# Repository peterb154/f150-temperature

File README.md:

# Ford F150 Temperature Display System

A production-ready Ford F150 temperature display system using ESP32-S3 with CAN bus integration and TFT display. This project provides a clean, automotive-grade interface showing outside air temperature, HVAC driver/passenger temperature settings, and fan speed with pixel-perfect text centering and professional styling.

## 🚗 Project Overview

This system captures and displays real-time Ford F150 climate control data via CAN bus at 125 kbps. It features a modern 4-card layout optimized for readability and includes special handling for HVAC off states, simulation mode for testing, and optional CSV logging for data analysis.

### Key Features

- **Real-time Temperature Display** - OAT, driver/passenger HVAC temps, and fan speed
- **Professional UI** - 4-card layout with pixel-perfect text centering and TrueType fonts
- **HVAC State Handling** - Blank display for disabled/off climate controls
- **Simulation Mode** - Built-in test mode cycling through various temperature scenarios
- **Adaptive Backlight** - PWM brightness control based on console dimming level
- **Optional CSV Logging** - Data capture for serial visualization tools (toggleable)
- **Parameterized Design** - Easy customization of fonts, colors, and layout

## 📁 Project Structure

```text
.
├── src/
│   ├── main.cpp                  # Production temperature display system
│   └── main.cpp.save.logger      # Original CAN logger (backup)
├── include/
│   ├── pins.h                    # Hardware pin assignments
│   └── colors.h                  # TFT display color definitions
├── can_visual_grid.py            # Python visualization tool (legacy)
├── F150_*.md                     # Decoded system documentation
│   ├── F150_CONSOLE_LIGHTS.md
│   ├── F150_HVAC_FAN.md
│   ├── F150_HVAC_TEMP.md
│   └── F150_OAT.md
├── platformio.ini                # ESP32 build configuration
├── pyproject.toml               # Python dependencies (for analysis tools)
└── README.md                    # This documentation
```

## 🔧 Hardware Requirements

### ESP32 Temperature Display Setup

- **ESP32-S3 Development Board** (320KB RAM, 8MB Flash recommended)
- **CAN Transceiver Module** (WCMCU-230 or MCP2551)
- **ILI9341 TFT Display** (320x240, SPI interface)
- **XPT2046 Touch Controller** (optional, for future expansion)

### Pin Configuration

Pin assignments are defined in `include/pins.h`:

```cpp
// CAN Bus pins
#define CAN_TX_PIN 47
#define CAN_RX_PIN 48

// ILI9341 Display pins
#define TFT_CS   45
#define TFT_RST  0
#define TFT_DC   35
#define TFT_MOSI 36
#define TFT_CLK  37
#define TFT_LED  38  // Backlight control
#define TFT_MISO 39

// Touch Controller pins (XPT2046)
#define TOUCH_CLK  40
#define TOUCH_CS   41
#define TOUCH_DIN  42
#define TOUCH_DO   2
#define TOUCH_IRQ  1

// Status LED
#define STATUS_LED_PIN 15
```

### Vehicle Connection

- **CAN High**: Connect to vehicle's CAN H line (used connection to car stereo)
- **CAN Low**: Connect to vehicle's CAN L line (used connection to car stereo)
- **Ground**: Connect to vehicle chassis ground
- **Power**: 12V from vehicle (with appropriate regulation to 3.3V/5V)

⚠️ **Important**: Use proper CAN bus termination and isolation, the MCU-230 has a built-in termination resistor. Always test on a non-critical vehicle first.

## 💻 Software Setup

### ESP32 Temperature Display Firmware

1. **Clone the repository** and navigate to the project directory
2. **Install PlatformIO** (if not already installed)
3. **Build and upload** the temperature display firmware:

    ```bash
    # Upload to ESP32-S3
    pio run --target upload

    # Monitor serial output (optional)
    pio device monitor
    ```

4. **Connect hardware** according to pin configuration above
5. **Power on** - the system will auto-start in simulation mode for testing
6. **Connect to vehicle CAN bus** to see live temperature data

### Main System Components

#### `src/main.cpp` - Temperature Display System

The main firmware provides a production-ready Ford F150 temperature display with:

- **4-Card Layout**: OAT (top-left), Driver Temp, Fan Speed, Passenger Temp (bottom row)
- **CAN Bus Integration**: Decodes Ford F150 PIDs at 125 kbps
  - `0x3C4` - Outside Air Temperature (bytes 6-7)
  - `0x3C8` - HVAC Driver/Passenger Temps (ASCII encoded, bytes 0-3)
  - `0x357` - Fan Speed (7 levels, byte 1)
  - `0x3B3` - Console Dim Level (PWM backlight control, byte 3)
- **Smart Display Logic**: Blank temperatures when HVAC is off/disabled
- **Adaptive Backlight**: PWM brightness based on console dimming
- **Simulation Mode**: Built-in test scenarios for development/demo

#### `include/pins.h` - Hardware Configuration

Centralized pin assignments for ESP32-S3 connections.

#### `include/colors.h` - Display Theme

Defines the professional color scheme using 16-bit RGB565 format:

- **COLOR_BACKGROUND** (`0x0841`) - Dark blue-grey background
- **COLOR_CARD_BG** (`0x2124`) - Lighter grey for temperature cards
- **COLOR_PRIMARY** (`0x07FF`) - Cyan accent color
- **COLOR_TEXT** (`0xFFFF`) - White text
- **COLOR_SUCCESS/WARNING/HOT** - Status and temperature-based colors

Colors can be easily customized by modifying the hex values in this file.

## 📊 System Features

### Temperature Display Layout

**4-Card Professional Interface:**
- **OAT Card** (top-left): Outside Air Temperature with "OAT" label
- **DRIVER Card** (bottom-left): Driver HVAC temperature setting
- **FAN Card** (bottom-center): Visual fan speed bars (7 levels)
- **PASS Card** (bottom-right): Passenger HVAC temperature setting

### Smart Display Features

- **Pixel-Perfect Centering**: All temperature values are precisely centered using TrueType fonts
- **Blank State Handling**: Cards show blank when HVAC is off or controls are disabled
- **Adaptive Backlight**: Display brightness automatically adjusts based on console dimming
- **Professional Styling**: Rounded cards, consistent spacing, automotive-grade appearance

### HVAC State Detection

- **HVAC Off**: When driver temp is 0x00,0x00, display shows blank and fan speed goes to 0
- **Passenger Disabled**: Passenger temp shows blank when controls are disabled
- **Normal Operation**: All temperatures display with clean numeric values (no "F" suffix)
- **Fan Visualization**: Horizontal bars indicate fan speed levels 0-7

### Simulation Mode

**Built-in Test Scenarios** (6-second cycles):
1. **Normal Operation** - All temps active, fan running
2. **HVAC System Off** - Driver blank, fan 0, passenger may be active
3. **Passenger Disabled** - Passenger blank, driver/fan normal
4. **All HVAC Off** - Both temps blank, fan 0
5. **Mixed States** - Various combinations for testing

### Optional CSV Logging

**Data Capture for Analysis:**
- **Toggle Control**: Set `enableCSVLogging = true` in code
- **CSV Format**: Timestamp, CAN ID, raw bytes, decoded temperatures
- **Serial Output**: Compatible with visualization tools
- **Performance**: Minimal overhead when enabled, zero when disabled

## 🔍 CAN Bus Analysis Tools

For reverse-engineering additional Ford F150 systems and analyzing CAN bus data, see the comprehensive analysis tools documentation:

**[CAN_ANALYSIS_README.md](CAN_ANALYSIS_README.md)**

Includes:
- Interactive CAN message visualization (`can_visual_grid.py`)
- Raw CAN logger firmware
- Complete reverse-engineering workflow
- Decoded system documentation
- Temperature calibration tools

## 🛠️ Usage

### Normal Operation

1. **Power On**: System starts automatically and shows simulation data
2. **Connect to Vehicle**: CAN bus connection switches to live data
3. **Display Updates**: Temperature cards update in real-time (10Hz refresh)
4. **Backlight Control**: Display brightness adapts to console dimming

### Configuration Options

**CSV Logging** (in `main.cpp`):

```cpp
bool enableCSVLogging = false;  // Set to true for data capture
```

**Simulation Mode** (forced during development):

```cpp
bool forceSimulation = true;   // Set to false for vehicle connection
```

### Hardware Customization

- **Pin Assignments**: Modify `include/pins.h` for different ESP32 boards
- **Display Colors**: Customize `include/colors.h` for different themes
- **Card Layout**: Adjust constants at top of `main.cpp` for sizing/positioning

## 🛠️ Troubleshooting

### Display Issues

**Blank or corrupted display:**

- Check SPI connections to ILI9341 (see `pins.h`)
- Verify power supply stability (3.3V/5V)
- Ensure correct pin definitions match your hardware

**No temperature updates:**

- Verify vehicle is running (systems sleep when off)
- Check CAN H/L connections and polarity
- Monitor serial output for CAN message reception
- Try simulation mode first (`forceSimulation = true`)

**Backlight not working:**

- Check TFT_LED pin connection (see `pins.h`)
- Verify PWM output is functioning
- Test with manual brightness setting

### Performance Issues

**Slow or flickering display:**

- Check power supply current capacity
- Verify SPI clock speed settings
- Monitor for memory issues in serial output

**CAN bus connection problems:**

- Ensure 125 kbps baud rate
- Verify CAN transceiver (MCU-230 recommended)
- Check termination resistance (120Ω)

### Development Tips

1. **Start with simulation mode** - validates display without vehicle
2. **Monitor serial output** - shows CAN status and decoded values
3. **Use CSV logging** - captures data for offline analysis
4. **Test incrementally** - verify each system (display, CAN, decoding) separately

## 🤝 License

MIT License

---

## Ready for your F150 dashboard! 🚗📊

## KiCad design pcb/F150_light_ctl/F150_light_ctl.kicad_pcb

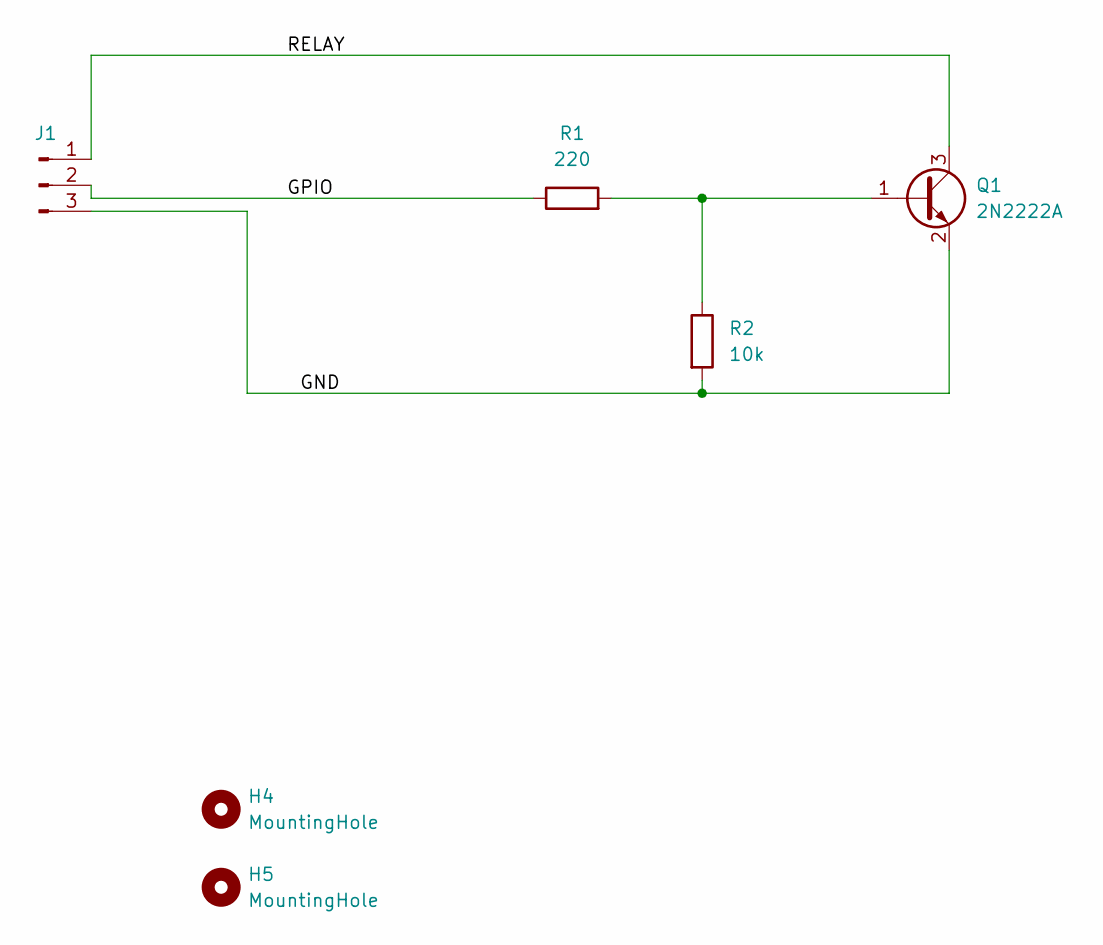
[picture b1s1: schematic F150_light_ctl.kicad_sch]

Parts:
H4, H5: MountingHole; MountingHole_3.5mm
J1: PinHeader_1x03_P2.54mm_Vertical
Q1: 2N2222A; SOT-23
R1: 220; R_0805_2012Metric
R2: 10k; R_0805_2012Metric

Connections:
/GND: J1.3, Q1.2 (E), R2.2
/GPIO: J1.2, R1.1
/RELAY: J1.1, Q1.3 (C)
unnamed: Q1.1 (B), R1.2, R2.1

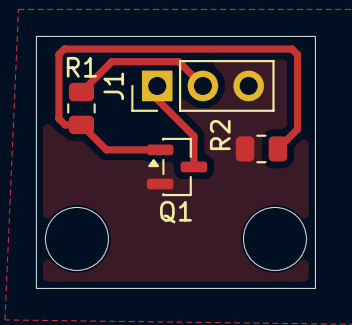
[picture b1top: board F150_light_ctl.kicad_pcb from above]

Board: 2 copper layers, 15.5 x 14.0 mm, 6 parts (0 on the bottom side), 4 nets.

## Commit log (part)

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2025-07-02 full logging
2025-07-03 working debugger
2025-07-03 Remove .pio build directory from version control
2025-07-07 working display
2025-07-08 working display in truck
2025-07-08 added images and stl files
